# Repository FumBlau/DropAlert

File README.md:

# DropAlert
Dispositivo de asistencia para su uso con perros guia

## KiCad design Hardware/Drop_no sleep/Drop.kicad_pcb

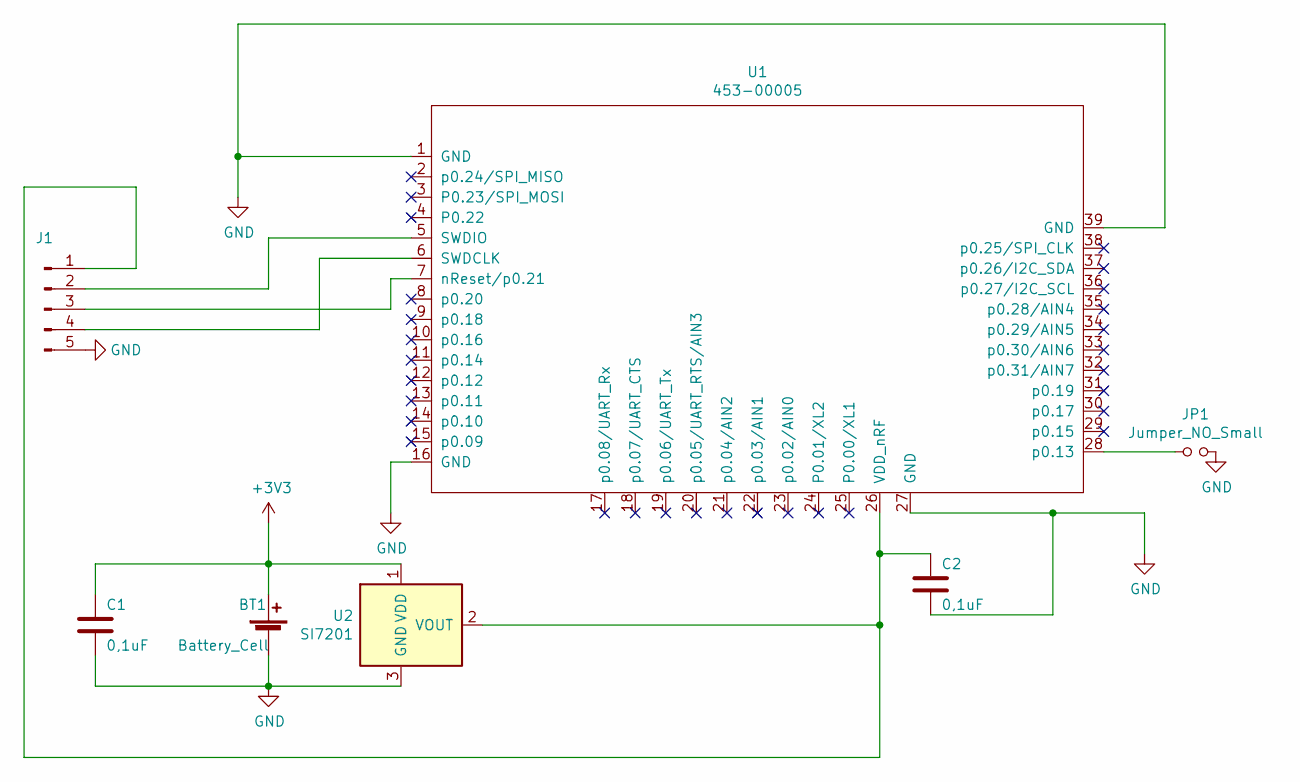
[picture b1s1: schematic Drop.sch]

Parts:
BT1: Battery_Cell; CR1216_holder_mouser_bat_hld_012_smt
C1, C2: 0,1uF; C_0603_1608Metric_Pad1.05x0.95mm_HandSolder
J1: Conn_01x05_Male; PinHeader_1x05_P1.27mm_Vertical
JP1: Jumper_NO_Small; SolderJumper-2_P1.3mm_Open_TrianglePad1.0x1.5mm
U1: 453-00005; 453-0005
U2: SI7201; SOT-23

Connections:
+3V3: BT1.1 (+), C1.1, U2.1 (VDD)
GND: BT1.2 (-), C1.2, C2.2, J1.5, JP1.2, U1.1 (GND), U1.16 (GND), U1.27 (GND), U1.39 (GND), U2.3 (GND)
unnamed: C2.1, J1.1, U1.26 (VDD_nRF), U2.2 (VOUT)
unnamed: J1.2, U1.5 (SWDIO)
unnamed: J1.3, U1.7 (nReset/p0.21)
unnamed: J1.4, U1.6 (SWDCLK)
unnamed: JP1.1, U1.28 (p0.13)

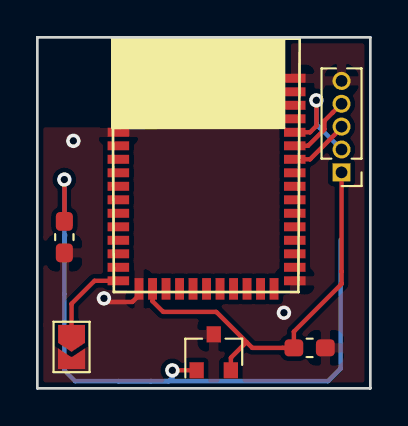
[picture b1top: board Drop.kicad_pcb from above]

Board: 2 copper layers, 18.5 x 19.5 mm, 7 parts (1 on the bottom side), 7 nets.

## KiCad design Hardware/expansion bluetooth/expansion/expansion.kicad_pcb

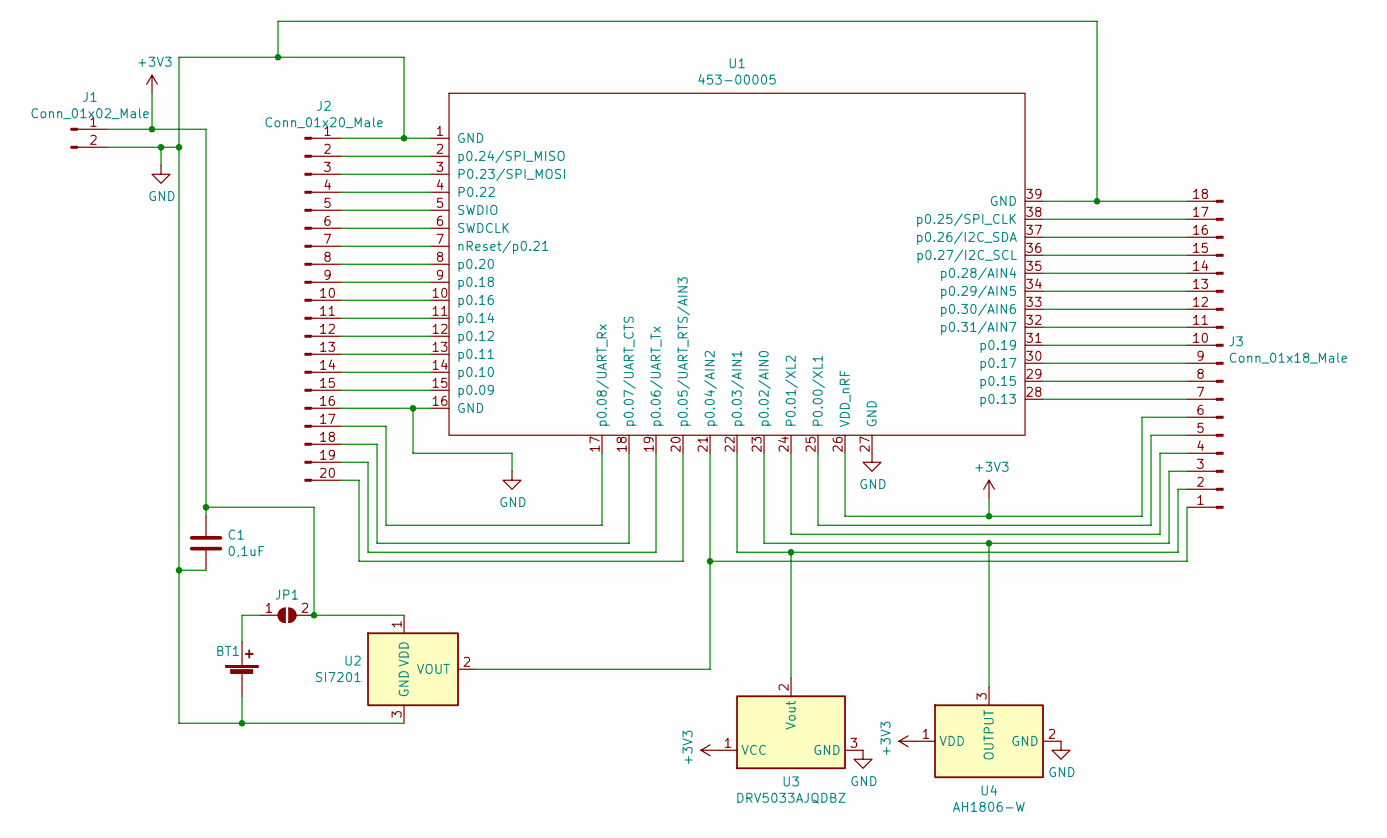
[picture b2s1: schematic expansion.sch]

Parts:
BT1: Battery_Cell; CR1216_holder_mouser_bat_hld_012_smt
C1: 0,1uF; C_0603_1608Metric_Pad1.05x0.95mm_HandSolder
J1: Conn_01x02_Male; PinHeader_1x02_P2.54mm_Vertical
J2: Conn_01x20_Male; PinHeader_1x20_P2.54mm_Vertical
J3: Conn_01x18_Male; PinHeader_1x18_P2.54mm_Vertical
JP1: SolderJumper_2_Open; SolderJumper-2_P1.3mm_Open_RoundedPad1.0x1.5mm
U1: 453-00005; 453-0005
U2: SI7201; SOT-23
U3: DRV5033AJQDBZ; SOT-23
U4: AH1806-W; SC-59

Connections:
+3V3: C1.1, J1.1, J3.6, JP1.2 (B), U1.26 (VDD_nRF), U2.1 (VDD), U3.1 (VCC), U4.1 (VDD)
GND: BT1.2 (-), C1.2, J1.2, J2.1, J2.16, J3.18, U1.1 (GND), U1.16 (GND), U1.27 (GND), U1.39 (GND), U2.3 (GND), U3.3 (GND), U4.2 (GND)
unnamed: BT1.1 (+), JP1.1 (A)
unnamed: J2.2, U1.2 (p0.24/SPI_MISO)
unnamed: J2.3, U1.3 (P0.23/SPI_MOSI)
unnamed: J2.4, U1.4 (P0.22)
unnamed: J2.5, U1.5 (SWDIO)
unnamed: J2.6, U1.6 (SWDCLK)
unnamed: J2.7, U1.7 (nReset/p0.21)
unnamed: J2.8, U1.8 (p0.20)
unnamed: J2.9, U1.9 (p0.18)
unnamed: J2.10, U1.10 (p0.16)
unnamed: J2.11, U1.11 (p0.14)
unnamed: J2.12, U1.12 (p0.12)
unnamed: J2.13, U1.13 (p0.11)
unnamed: J2.14, U1.14 (p0.10)
unnamed: J2.15, U1.15 (p0.09)
unnamed: J2.17, U1.17 (p0.08/UART_Rx)
unnamed: J2.18, U1.18 (p0.07/UART_CTS)
unnamed: J2.19, U1.19 (p0.06/UART_Tx)
unnamed: J2.20, U1.20 (p0.05/UART_RTS/AIN3)
unnamed: J3.1, U1.21 (p0.04/AIN2), U2.2 (VOUT)
unnamed: J3.2, U1.22 (p0.03/AIN1), U3.2 (Vout)
unnamed: J3.3, U1.23 (p0.02/AIN0), U4.3 (OUTPUT)
unnamed: J3.4, U1.24 (P0.01/XL2)
unnamed: J3.5, U1.25 (P0.00/XL1)
unnamed: J3.7, U1.28 (p0.13)
unnamed: J3.8, U1.29 (p0.15)
unnamed: J3.9, U1.30 (p0.17)
unnamed: J3.10, U1.31 (p0.19)
unnamed: J3.11, U1.32 (p0.31/AIN7)
unnamed: J3.12, U1.33 (p0.30/AIN6)
unnamed: J3.13, U1.34 (p0.29/AIN5)
unnamed: J3.14, U1.35 (p0.28/AIN4)
unnamed: J3.15, U1.36 (p0.27/I2C_SCL)
unnamed: J3.16, U1.37 (p0.26/I2C_SDA)
unnamed: J3.17, U1.38 (p0.25/SPI_CLK)

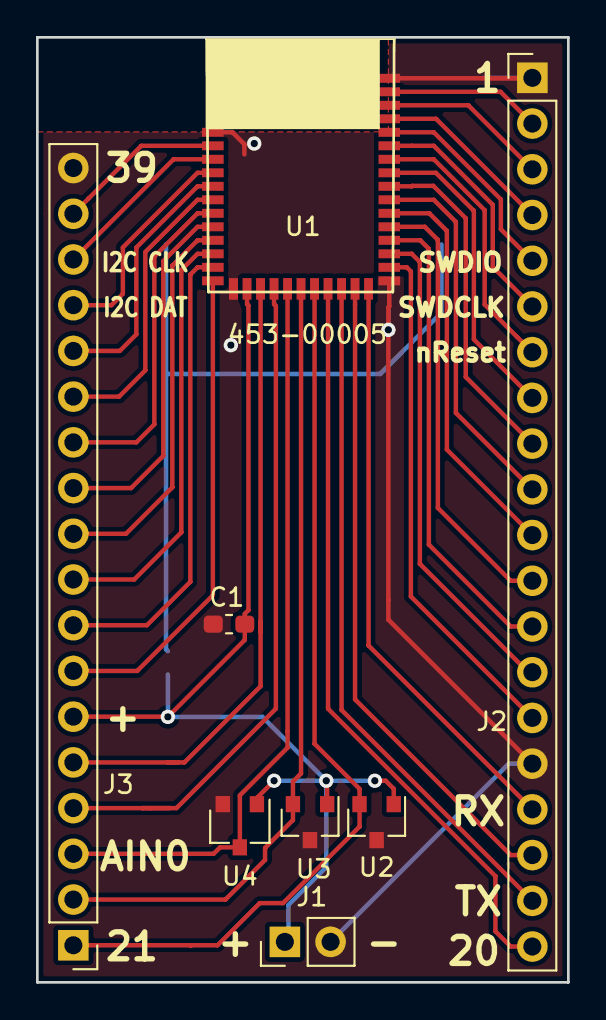
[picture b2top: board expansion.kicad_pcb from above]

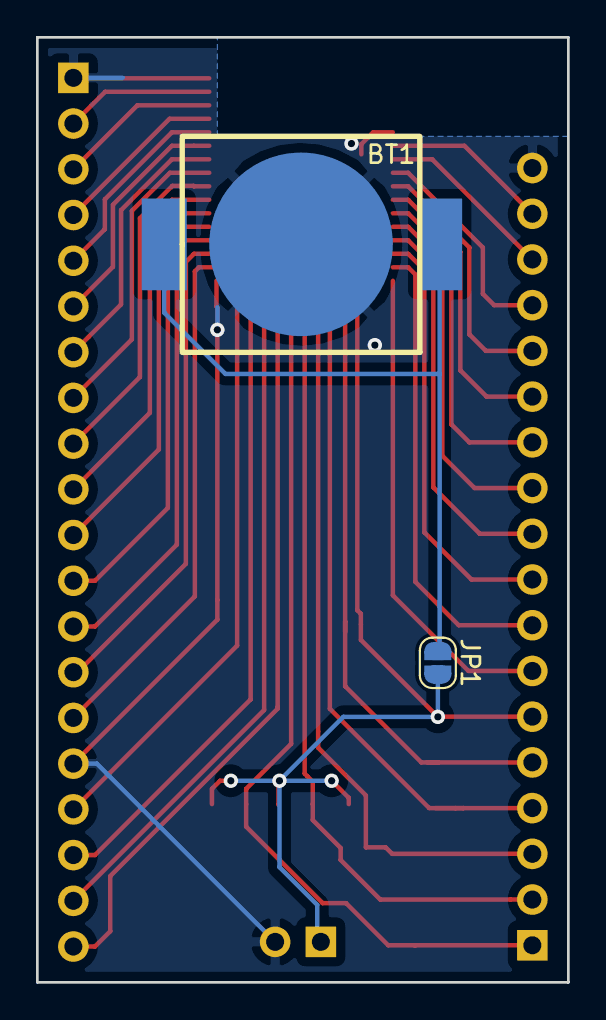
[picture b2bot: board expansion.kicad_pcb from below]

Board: 2 copper layers, 29.5 x 52.5 mm, 10 parts (2 on the bottom side), 37 nets.

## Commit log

2019-03-11 Adds initial react native app.
2019-03-11 Extracts the configuration form from the main app file to a new component.
2019-03-11 Makes more logical the behaviour of the phone validation and saving messages.
2019-03-11 Adds tests for the ConfigForm component.
2019-03-11 Fixes icon after upgrading packages.
2019-03-18 Fix problem with the mobile icon in form
2019-03-18 Replaces project bootstrap with Expo with a pure react native with Android support.
2019-03-18 Updates gitignore
2019-03-25 Updates gitignore to properly ignore android folders
2019-03-25 Improves .gitignore
2019-03-25 Removes unnecessary folders.
2019-03-25 Adds first version of the ConnectButton.js
2019-03-25 Tries to fix the bluetooth scanning
2019-03-25 First steps to connect devices via bluetooth
2019-03-27 Add GeoLocation to DropAlert app
2019-03-27 Remove continuos scan in GeoLocationButton component
2019-03-27 Send SMS programatically with the location
2019-04-10 Adds support for detecting Eddystone UID beacons.
2019-04-12 Extract to service react native libraries
2019-04-12 Fixes several syntax errors.
2019-04-12 Fixes compilation error due to component not correctly initialized.
2019-04-12 Fix errors when extract libraries to services
2019-04-17 Bluetooth now scans on the background and sends the SMS when the bluetooth is detected.
2019-04-17 Replaces AsyncStorage library to use new contributed library due to deprecation. Fixes loading of phone storage when sending SMS.
2019-04-17 adds support to send SMSs to multiple phones.
2019-04-17 Improves styling of the application.
2019-05-22 Beta 1 de hardware
2019-06-13 - a angel no se le ve nada
2019-06-28 - Añado versión no-sleep
2019-07-10 - Añado v1 de encapsulado
2019-10-03 - junto mi pc con remoto
2019-10-03 - Añado .apk e informe
2019-10-03 Bump lodash from 4.17.11 to 4.17.15 in /app
    Bumps [lodash](https://github.com/lodash/lodash) from 4.17.11 to 4.17.15.
    - [Release notes](https://github.com/lodash/lodash/releases)
    - [Commits](https://github.com/lodash/lodash/compare/4.17.11...4.17.15)
2019-10-03 Updates versions of npm packages to remove security warnings
2019-10-03 Bump handlebars from 4.1.1 to 4.4.2 in /app
    Bumps [handlebars](https://github.com/wycats/handlebars.js) from 4.1.1 to 4.4.2.
    - [Release notes](https://github.com/wycats/handlebars.js/releases)
    - [Changelog](https://github.com/wycats/handlebars.js/blob/v4.4.2/release-notes.md)
    - [Commits](https://github.com/wycats/handlebars.js/compare/v4.1.1...v4.4.2)
2019-10-03 Bump js-yaml from 3.12.2 to 3.13.1 in /app
    Bumps [js-yaml](https://github.com/nodeca/js-yaml) from 3.12.2 to 3.13.1.
    - [Release notes](https://github.com/nodeca/js-yaml/releases)
    - [Changelog](https://github.com/nodeca/js-yaml/blob/master/CHANGELOG.md)
    - [Commits](https://github.com/nodeca/js-yaml/compare/3.12.2...3.13.1)
2019-10-03 Bump mixin-deep from 1.3.1 to 1.3.2 in /app
    Bumps [mixin-deep](https://github.com/jonschlinkert/mixin-deep) from 1.3.1 to 1.3.2.
    - [Release notes](https://github.com/jonschlinkert/mixin-deep/releases)
    - [Commits](https://github.com/jonschlinkert/mixin-deep/compare/1.3.1...1.3.2)
2019-12-28 Bump handlebars from 4.1.1 to 4.5.3 in /app
    Bumps [handlebars](https://github.com/wycats/handlebars.js) from 4.1.1 to 4.5.3.
    - [Release notes](https://github.com/wycats/handlebars.js/releases)
    - [Changelog](https://github.com/wycats/handlebars.js/blob/master/release-notes.md)
    - [Commits](https://github.com/wycats/handlebars.js/compare/v4.1.1...v4.5.3)
2020-03-14 Bump acorn from 5.7.3 to 5.7.4 in /app
    Bumps [acorn](https://github.com/acornjs/acorn) from 5.7.3 to 5.7.4.
    - [Release notes](https://github.com/acornjs/acorn/releases)
    - [Commits](https://github.com/acornjs/acorn/compare/5.7.3...5.7.4)
2020-09-04 Bump handlebars from 4.1.1 to 4.7.6 in /app
    Bumps [handlebars](https://github.com/wycats/handlebars.js) from 4.1.1 to 4.7.6.
    - [Release notes](https://github.com/wycats/handlebars.js/releases)
    - [Changelog](https://github.com/handlebars-lang/handlebars.js/blob/master/release-notes.md)
    - [Commits](https://github.com/wycats/handlebars.js/compare/v4.1.1...v4.7.6)
2021-03-30 Bump y18n from 3.2.1 to 3.2.2 in /app
    Bumps [y18n](https://github.com/yargs/y18n) from 3.2.1 to 3.2.2.
    - [Release notes](https://github.com/yargs/y18n/releases)
    - [Changelog](https://github.com/yargs/y18n/blob/master/CHANGELOG.md)
    - [Commits](https://github.com/yargs/y18n/commits)
2021-05-06 Bump ua-parser-js from 0.7.19 to 0.7.28 in /app
    Bumps [ua-parser-js](https://github.com/faisalman/ua-parser-js) from 0.7.19 to 0.7.28.
    - [Release notes](https://github.com/faisalman/ua-parser-js/releases)
    - [Commits](https://github.com/faisalman/ua-parser-js/compare/0.7.19...0.7.28)
2021-05-07 Bump handlebars from 4.1.1 to 4.7.7 in /app
    Bumps [handlebars](https://github.com/wycats/handlebars.js) from 4.1.1 to 4.7.7.
    - [Release notes](https://github.com/wycats/handlebars.js/releases)
    - [Changelog](https://github.com/handlebars-lang/handlebars.js/blob/master/release-notes.md)
    - [Commits](https://github.com/wycats/handlebars.js/compare/v4.1.1...v4.7.7)
2021-05-08 Bump lodash from 4.17.11 to 4.17.21 in /app
    Bumps [lodash](https://github.com/lodash/lodash) from 4.17.11 to 4.17.21.
    - [Release notes](https://github.com/lodash/lodash/releases)
    - [Commits](https://github.com/lodash/lodash/compare/4.17.11...4.17.21)
2021-05-10 Bump hosted-git-info from 2.7.1 to 2.8.9 in /app
    Bumps [hosted-git-info](https://github.com/npm/hosted-git-info) from 2.7.1 to 2.8.9.
    - [Release notes](https://github.com/npm/hosted-git-info/releases)
    - [Changelog](https://github.com/npm/hosted-git-info/blob/v2.8.9/CHANGELOG.md)
    - [Commits](https://github.com/npm/hosted-git-info/compare/v2.7.1...v2.8.9)
2021-07-20 Bump react-native from 0.59.2 to 0.62.3 in /app
    Bumps [react-native](https://github.com/facebook/react-native) from 0.59.2 to 0.62.3.
    - [Release notes](https://github.com/facebook/react-native/releases)
    - [Changelog](https://github.com/facebook/react-native/blob/main/Releases.md)
    - [Commits](https://github.com/facebook/react-native/compare/v0.59.2...v0.62.3)
    ---
    updated-dependencies:
2021-08-10 Bump path-parse from 1.0.6 to 1.0.7 in /app
    Bumps [path-parse](https://github.com/jbgutierrez/path-parse) from 1.0.6 to 1.0.7.
    - [Release notes](https://github.com/jbgutierrez/path-parse/releases)
    - [Commits](https://github.com/jbgutierrez/path-parse/commits/v1.0.7)
    ---
    updated-dependencies:
    - dependency-name: path-parse
2021-09-21 Bump tmpl from 1.0.4 to 1.0.5 in /app
    Bumps [tmpl](https://github.com/daaku/nodejs-tmpl) from 1.0.4 to 1.0.5.
    - [Release notes](https://github.com/daaku/nodejs-tmpl/releases)
    - [Commits](https://github.com/daaku/nodejs-tmpl/commits/v1.0.5)
    ---
    updated-dependencies:
    - dependency-name: tmpl
2022-02-10 Bump ua-parser-js from 0.7.19 to 0.7.31 in /app
    Bumps [ua-parser-js](https://github.com/faisalman/ua-parser-js) from 0.7.19 to 0.7.31.
    - [Release notes](https://github.com/faisalman/ua-parser-js/releases)
    - [Commits](https://github.com/faisalman/ua-parser-js/compare/0.7.19...0.7.31)
    ---
    updated-dependencies:
    - dependency-name: ua-parser-js
2022-02-11 Bump ajv from 6.10.0 to 6.12.6 in /app
    Bumps [ajv](https://github.com/ajv-validator/ajv) from 6.10.0 to 6.12.6.
    - [Release notes](https://github.com/ajv-validator/ajv/releases)
    - [Commits](https://github.com/ajv-validator/ajv/compare/v6.10.0...v6.12.6)
    ---
    updated-dependencies:
    - dependency-name: ajv
2022-03-01 Bump plist from 3.0.1 to 3.0.4 in /app
    Bumps [plist](https://github.com/TooTallNate/node-plist) from 3.0.1 to 3.0.4.
    - [Release notes](https://github.com/TooTallNate/node-plist/releases)
    - [Changelog](https://github.com/TooTallNate/plist.js/blob/master/History.md)
    - [Commits](https://github.com/TooTallNate/node-plist/commits)
    ---
    updated-dependencies:
2022-04-28 Bump async from 2.6.2 to 2.6.4 in /app
    Bumps [async](https://github.com/caolan/async) from 2.6.2 to 2.6.4.
    - [Release notes](https://github.com/caolan/async/releases)
    - [Changelog](https://github.com/caolan/async/blob/v2.6.4/CHANGELOG.md)
    - [Commits](https://github.com/caolan/async/compare/v2.6.2...v2.6.4)
    ---
    updated-dependencies:
2022-06-02 Bump simple-plist from 1.0.0 to 1.3.1 in /app
    Bumps [simple-plist](https://github.com/wollardj/simple-plist) from 1.0.0 to 1.3.1.
    - [Release notes](https://github.com/wollardj/simple-plist/releases)
    - [Commits](https://github.com/wollardj/simple-plist/compare/v1.0.0...v1.3.1)
    ---
    updated-dependencies:
    - dependency-name: simple-plist
2022-10-11 Bump xmldom and plist in /app
    Removes [xmldom](https://github.com/xmldom/xmldom). It's no longer used after updating ancestor dependency [plist](https://github.com/TooTallNate/node-plist). These dependencies need to be updated to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
    Removes `xmldom`
    Updates `plist` from 3.0.1 to 3.0.6
    - [Release notes](https://github.com/TooTallNate/node-plist/releases)
    - [Changelog](https://github.com/TooTallNate/plist.js/blob/master/History.md)
    - [Commits](https://github.com/TooTallNate/node-plist/commits)
2022-12-03 Bump decode-uri-component from 0.2.0 to 0.2.2 in /app
    Bumps [decode-uri-component](https://github.com/SamVerschueren/decode-uri-component) from 0.2.0 to 0.2.2.
    - [Release notes](https://github.com/SamVerschueren/decode-uri-component/releases)
    - [Commits](https://github.com/SamVerschueren/decode-uri-component/compare/v0.2.0...v0.2.2)
    ---
    updated-dependencies:
    - dependency-name: decode-uri-component
2022-12-08 Bump qs from 6.5.2 to 6.5.3 in /app
    Bumps [qs](https://github.com/ljharb/qs) from 6.5.2 to 6.5.3.
    - [Release notes](https://github.com/ljharb/qs/releases)
    - [Changelog](https://github.com/ljharb/qs/blob/main/CHANGELOG.md)
    - [Commits](https://github.com/ljharb/qs/compare/v6.5.2...v6.5.3)
    ---
    updated-dependencies:
2023-01-03 Bump json5 from 2.1.0 to 2.2.3 in /app
    Bumps [json5](https://github.com/json5/json5) from 2.1.0 to 2.2.3.
    - [Release notes](https://github.com/json5/json5/releases)
    - [Changelog](https://github.com/json5/json5/blob/main/CHANGELOG.md)
    - [Commits](https://github.com/json5/json5/compare/v2.1.0...v2.2.3)
    ---
    updated-dependencies:
